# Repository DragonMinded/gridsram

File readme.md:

A set of utilities for interfacing with a M48Z128-85PM1 battery-backed SRAM chip that has been used in The Grid by Midway. This is the chip that stores all of the player profiles so that players can track their statistics, name and call name across different games. It also stores all the single player tower clear records for the cabinet. The ``ArduinoSRAMReader`` directory contains an Arduino sketch that can interface with the ``dump.py`` utility inside the ``GridUtilities`` directory. When used together, an SRAM chip can be partially or fully read or written. The ``print.py`` utility takes a dumped 128KB SRAM file (or a MAME ``nvram`` file) and prints profiles and tower clear records contained in it. The ``editor.py`` utility presents a curses interface where you can add, edit and delete profiles from an SRAM file (or a MAME ``nvram`` file) as well as reset tower clear records for various towers.

All of the scripts require Python 3.6 or greater due to their use of type hints. The ``editor.py`` script additionally requires that [dragoncurses](https://github.com/DragonMinded/dragoncurses) be installed. All utilites are meant to be run from the commandline and all utilities include help. Edited profiles are fully compatible with both the emulated MAME release of The Grid as well as actual arcade hardware. If everything is working correctly, it should take about a minute to dump a full SRAM chip and about a minute and a half to write a full SRAM chip.

## Running the Utilities

Utilities can all be run from the commandline on any operating system with Python 3.6 or greater in the path. All of them support help, so you should start by running any of the utilities with the "--help" flag in order to see more of the utility's operation. All utilities should be run from within the `GridUtilities` folder.

### dump.py

A simple utility that can interface with hardware as built below and plugged into a programmed Arduino. It can perform a read or a write action. Run it like so to see options:

```
python3 dump.py --help
```

Note that depending on your operating system, the default port will not work and you will have to specify it directly. On MacOS and Linux, you can run `ls /dev/tty*` and your Arduino will probably be the only one listed. On Windows, you will have to specify the com port such as "COM1" that the Arduino is connected to.

### print.py

A simple parsing utility that will read an SRAM dumped from "dump.py" or taken from MAME and print out one or more profiles and tower clear records contained inside it. Run it like so to see options:

```
python3 print.py --help
```

### editor.py

A text-based UI for editing profiles on a SRAM dumped from "dump.py" or taken from MAME. Note that this requires [dragoncurses](https://github.com/DragonMinded/dragoncurses) be installed in order to operate properly! It can create new profiles, delete profiles, and edit the details of any existing profile including the PIN, name, call sign and other details. Run it like so to see options:

```
python3 editor.py --help
```

## Arduino Schematic for Real Hardware

The following is a simple schematic that I built in order to edit profiles on an SRAM chip that I had in my posession. I've connected the 8 bidirectional data lines directly to 8 Arduino pins. I've connected two Arduino pins through inverters to the write enable and output enable lines to programatically select read/write mode. I've connected two Arduino pins to three serial to parallel shift registers in order to drive the necessary 17 address lines from two Arduino pins. If you use the same Arduino line, tied directly to the output enable line, and through an inverter to the write enable line (ensuring startup defaults to read), you can probably get away with using only two shift registers and tying A16 directly to the unused Arduino pin. I have not tested this. I have not included decoupling capacitors or a power supply. I recommend 0.1uF decoupling capacitors for each chip including the M48Z128. The datasheet for the SRAM also recommends a 1N5817 diode connected between its VCC and GND pins to protect against data loss when powering the chip. You should be able to take +5V and GND from the Arduino and it will supply enough voltage. I assume that you can either build your own CMOS inverters using BJTs or use a 7400 series inverter chip such as a quad NAND gate with both inputs tied together for each gate. When referring to a free floating pin, this indicates a connection to an Arduino Uno pin. In order to make an ASCII diagram possible, connections between the 74LS164 shift registers handling the address logic and the M48Z128 chip are not drawn. Instead they are labelled. It goes without saying but if you use an external PSU to provide +5V, connect the grounds from the Arduino, all of the ground points in the diagram, and the PSU.

                                                        o +5V pin
                           +-----------------------+    |
                           |1  NC            VCC 32|----/
      74LS164 3 Qa (3)-----|2  A16           A15 31|-----74LS164 2 Qh (13)
     74LS164 2 Qg (12)-----|3  A14            NC 30|                                           /|
     74LS164 2 Qe (10)-----|4  A12            !W 29|-----------------------------------------o |-----o Pin 12
     74LS164 1 Qh (13)-----|5  A7      M     A13 28|-----74LS164 2 Qf (11)                     \|
     74LS164 1 Qg (12)-----|6  A6      4      A8 27|-----74LS164 2 Qa (3)
     74LS164 1 Qf (11)-----|7  A5      8      A9 26|-----74LS164 2 Qb (4)
     74LS164 1 Qe (10)-----|8  A4      Z     A11 25|-----74LS164 2 Qd (6)                      /|
      74LS164 1 Qd (6)-----|9  A3      1      !G 24|-----------------------------------o |-----o Analog Pin 2
      74LS164 1 Qc (5)-----|10 A2      2     A10 23|-----74LS164 2 Qc (5)                      \|
      74LS164 1 Qb (4)-----|11 A1      8      !E 22|----------------o GND (chip always enbled)
      74LS164 1 Qa (3)-----|12 A0            DQ7 21|-----o Pin 9
               Pin 2 o-----|13 DQ0           DQ6 20|-----o Pin 8
               Pin 3 o-----|14 DQ1           DQ5 19|-----o Pin 7
               Pin 4 o-----|15 DQ2           DQ4 18|-----o Pin 6
                      /----|16 GND           DQ3 17|-----o Pin 5
                      |    +-----------------------+
              GND pin o
   
                                   74LS164 1         o +5V pin
                              +-----------------+    |
                 Pin 10 o-----|1  A       VCC 14|----/
     +5V pin o----------------|2  B        Qh 13|-----A7 (5) and 74LS164 2 A (1)
                  A0 (12)-----|3  Qa       Qg 12|-----A6 (6)
                  A1 (11)-----|4  Qb       Qf 11|-----A5 (7)
                  A2 (10)-----|5  Qc       Qe 10|-----A4 (8)
                   A3 (9)-----|6  Qd     !CLR  9|---------------o +5V pin
                         /----|7  GND     CLK  8|-----o Pin 11
                         |    +-----------------+
                 GND pin o
   
                                   74LS164 2         o +5V pin
                              +-----------------+    |
        74LS164 1 Qh (13)-----|1  A       VCC 14|----/
     +5V pin o----------------|2  B        Qh 13|-----A15 (31) and 74LS164 3 A (1)
                  A8 (27)-----|3  Qa       Qg 12|-----A14 (3)
                  A9 (26)-----|4  Qb       Qf 11|-----A13 (28)
                 A10 (23)-----|5  Qc       Qe 10|-----A12 (4)
                 A11 (25)-----|6  Qd     !CLR  9|---------------o +5V pin
                         /----|7  GND     CLK  8|-----o Pin 11
                         |    +-----------------+
                 GND pin o
   
                                   74LS164 3         o +5V pin
                              +-----------------+    |
      74LS164 2 Qh (13) o-----|1  A       VCC 14|----/
     +5v pin o----------------|2  B        Qh 13|
                  A16 (2)-----|3  Qa       Qg 12|
                              |4  Qb       Qf 11|
                              |5  Qc       Qe 10|
                              |6  Qd     !CLR  9|---------------o Connect to +5v to disable
                         /----|7  GND     CLK  8|-----o Pin 11
                         |    +-----------------+
                 GND pin o

## PCB and KiCad Schematic

If you don't want to hand-wire a circuit, I have tested out an Arduino shield board that you can have manufactured and then assemble yourself. If you just want to get a board manufactured, check out https://oshpark.com/shared_projects/tCR4N9Gb which has the BOM as well as the board laid out and ready to be ordered. You will still need to assemble the board yourself which requires some soldering experience. For the source files (made in KiCad), check out the `Board/` folder.

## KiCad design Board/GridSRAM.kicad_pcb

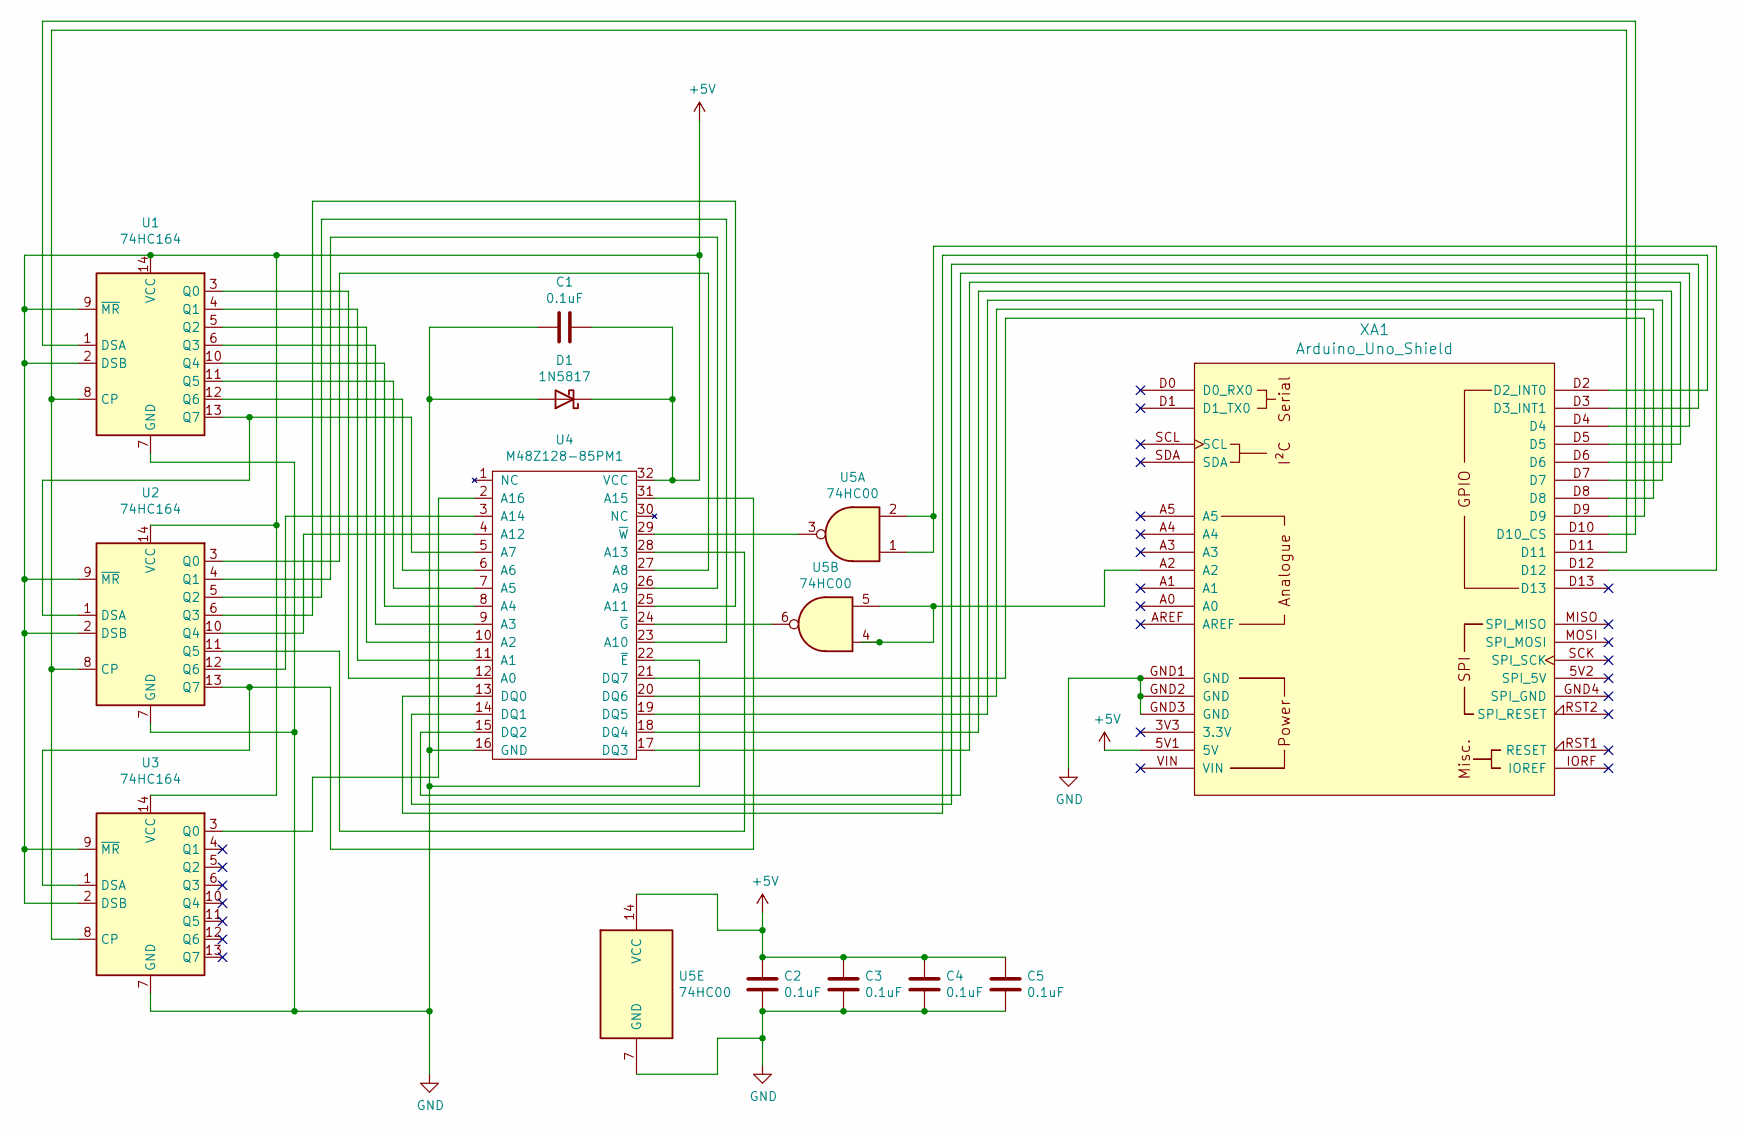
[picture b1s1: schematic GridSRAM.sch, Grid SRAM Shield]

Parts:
C1, C2, C3, C4, C5: 0.1uF; C_Disc_D4.3mm_W1.9mm_P5.00mm
D1: 1N5817; D_DO-41_SOD81_P10.16mm_Horizontal
U1, U2, U3: 74HC164; DIP-14_W7.62mm_Socket
U4: M48Z128-85PM1
U5: 74HC00; DIP-14_W7.62mm_Socket
XA1: Arduino_Uno_Shield

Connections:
+5V: C1.1, C2.1, C3.1, C4.1, C5.1, D1.1 (K), U1.2 (DSB), U1.9 (~MR), U1.14 (VCC), U2.2 (DSB), U2.9 (~MR), U2.14 (VCC), U3.2 (DSB), U3.9 (~MR), U3.14 (VCC), U4.32 (VCC), U5.14 (VCC), XA1.5V1 (5V)
GND: C1.2, C2.2, C3.2, C4.2, C5.2, D1.2 (A), U1.7 (GND), U2.7 (GND), U3.7 (GND), U4.16 (GND), U4.22 (~E), U5.7 (GND), XA1.GND1 (GND), XA1.GND2 (GND), XA1.GND3 (GND)
unnamed: U1.1 (DSA), XA1.D10 (D10_CS)
unnamed: U1.3 (Q0), U4.12 (A0)
unnamed: U1.4 (Q1), U4.11 (A1)
unnamed: U1.5 (Q2), U4.10 (A2)
unnamed: U1.6 (Q3), U4.9 (A3)
unnamed: U1.8 (CP), U2.8 (CP), U3.8 (CP), XA1.D11
unnamed: U1.10 (Q4), U4.8 (A4)
unnamed: U1.11 (Q5), U4.7 (A5)
unnamed: U1.12 (Q6), U4.6 (A6)
unnamed: U1.13 (Q7), U2.1 (DSA), U4.5 (A7)
unnamed: U2.3 (Q0), U4.27 (A8)
unnamed: U2.4 (Q1), U4.26 (A9)
unnamed: U2.5 (Q2), U4.23 (A10)
unnamed: U2.6 (Q3), U4.25 (A11)
unnamed: U2.10 (Q4), U4.4 (A12)
unnamed: U2.11 (Q5), U4.28 (A13)
unnamed: U2.12 (Q6), U4.3 (A14)
unnamed: U2.13 (Q7), U3.1 (DSA), U4.31 (A15)
unnamed: U3.3 (Q0), U4.2 (A16)
unnamed: U4.13 (DQ0), XA1.D2 (D2_INT0)
unnamed: U4.14 (DQ1), XA1.D3 (D3_INT1)
unnamed: U4.15 (DQ2), XA1.D4
unnamed: U4.17 (DQ3), XA1.D5
unnamed: U4.18 (DQ4), XA1.D6
unnamed: U4.19 (DQ5), XA1.D7
unnamed: U4.20 (DQ6), XA1.D8
unnamed: U4.21 (DQ7), XA1.D9
unnamed: U4.24 (~G), U5.6
unnamed: U4.29 (~W), U5.3
unnamed: U5.1, U5.2, XA1.D12
unnamed: U5.4, U5.5, XA1.A2

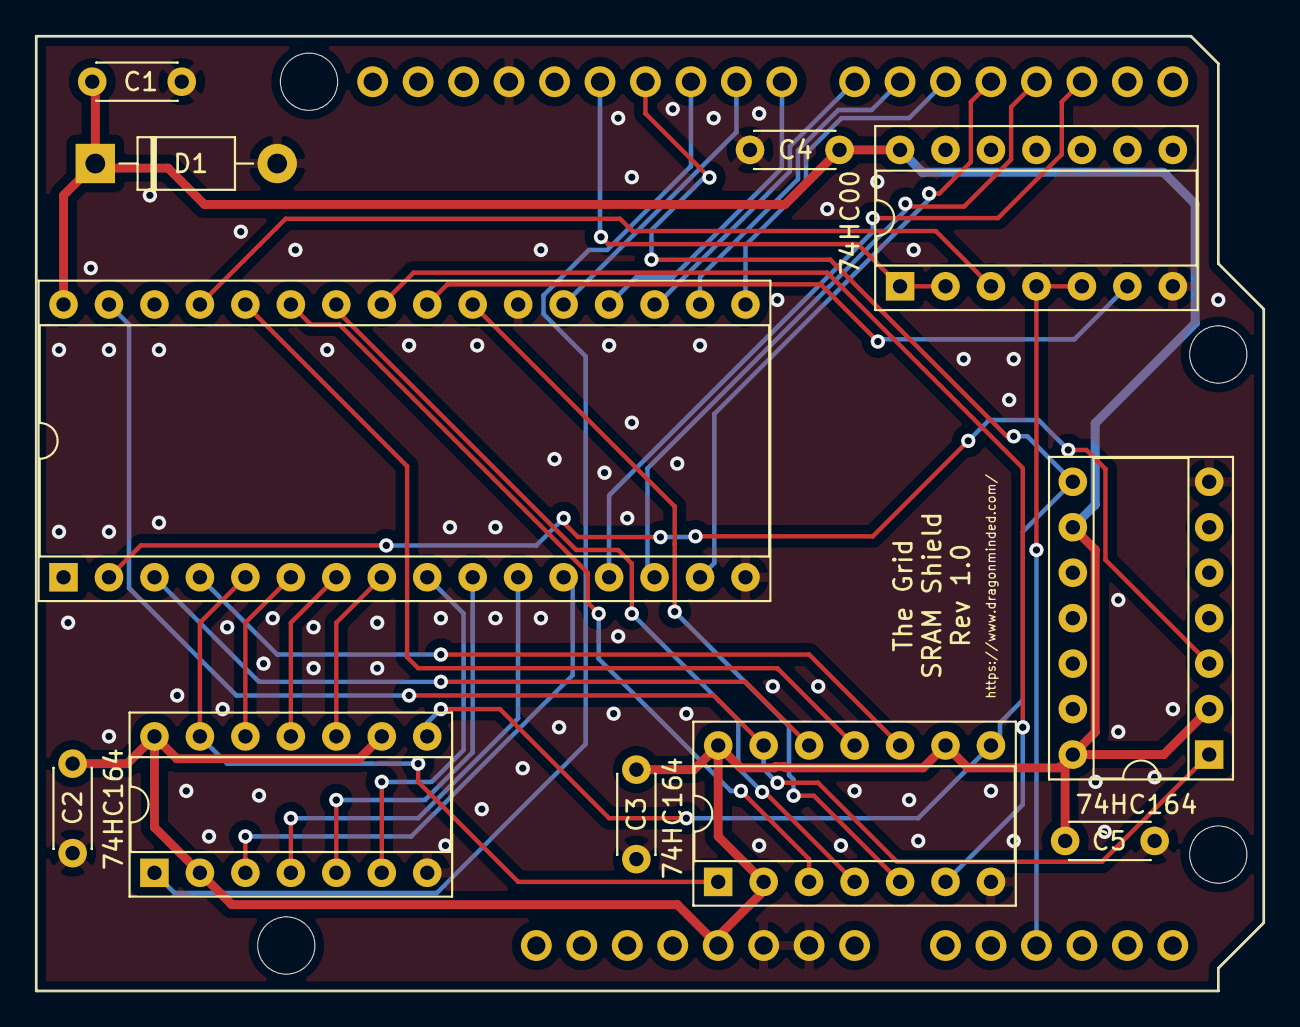
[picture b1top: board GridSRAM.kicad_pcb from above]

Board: 2 copper layers, 68.6 x 53.3 mm, 12 parts (0 on the bottom side), 33 nets.

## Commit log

2019-01-04 Initial commit of protocol.
2019-01-05 Add a .gitignore.
2019-01-05 Hook up to digital IO and shift registers to actually read SRAM chip.
2019-01-05 Bugfix for reading small values, add byte/wordswap utilities.
2019-01-05 Add a dump utility to start exercising code.
2019-01-11 Hook up OE/WE and implement chip write.
2019-01-11 Fix bug where we don't recognize an error response during a continue.
2019-01-13 Split byte utilities out to their own file.
2019-01-13 Initial check-in of profile RE.
2019-01-13 Apply some flake8 and mypy fixes.
2019-01-26 Ignore mypy files.
2019-01-26 Allow hex specification of offset/length as well as decimal.
2019-01-26 Fix horrid global reference, support scanning entire chip for profiles.
2019-02-02 Additional reverse engineering of the profile format.
2019-02-02 Additional profile reverse engineering complete.
2019-02-03 Clean up profile code, add frontend utility, add profile collection helper.
2019-02-03 Add another reversed field, make printout prettier.
2019-02-03 Finish RE on important fields.
2019-02-03 Add documentation for the rest of the fields.
2019-02-03 Make profile create set the data flag correctly.
2019-02-03 Proper profile limit, plus preserve the rest of the chip.
2019-02-05 Finish RE on 3 of the 4 remaining bytes, document the last one. Fix up clearing a profile to not create a new object reference and also properly initialize the checksum.
2019-02-05 Rename grid utilities directory to be more accurate.
2019-02-05 Better help for print utility.
2019-02-05 Add initial version of profile editor. Currently can display profiles on a list and delete them.
2019-02-06 Allow clicking on the profile list to select.
2019-02-06 Slight improvements to grid list component.
2019-02-06 Minor fixes to profile object.
2019-02-06 Hook up editor dialog with validation and such.
2019-02-06 Hook up the ability to add a new profile.
2019-02-07 Add ability to change control mode. Fix clicking on main profile to properly constrain to the list.
2019-02-07 Real fix for idle CPU usage applied to dragoncurses upstream.
2019-02-09 Apply caching to speed up rendering list.
2019-02-09 Handle scroll window for profile list.
2019-02-09 Fix delete not busting cache, add home/end/pgup/pgdn support to list.
2019-02-09 Address todos by inserting LUT for call sign to call name.
2019-02-09 Add right click context menu to grid list.
2019-02-09 Support double-click to edit.
2019-02-09 Add support for scrolling with mouse.
2019-02-09 Make script frontends executable.
2019-02-09 Add a readme for the project.
2019-02-09 Put the readme in the right place -_-;
2019-02-09 Better fit for schematic.
2019-02-09 Format schematic a bit more.
2019-02-09 Consistency in VCC/GND for all chips.
2020-08-09 Fix inability to create a new profile on an empty SRAM file.
2021-01-02 Move OE pin to Analog Pin 2 to avoid flickering LED problem with pin 13.
2021-01-02 Add additional details for schematic.
2021-01-03 Get rid of unnecessary delays, speed up reading/writing by a bunch.
2021-01-03 Fix writes that need slower data transmission, update readme with expected read and write times.
2021-01-20 Update readme with link to PCB.
2021-01-20 Add KiCad project so sources for PCB are available.
2021-06-27 Remove unrelated binary utilities so I can move them to arcadeutils.
2022-04-15 Update readme with more details on running utilities.
2022-04-15 Update editor to allow for tower level 10 to be selected, also allow creating an SRAM file from scratch when editing.
2022-04-23 Add requirements.txt file for running the utilities, ignore SRAM dumps.
2022-08-06 Fix problem reading/writing 10 digit PINs when the first digit is non-zero.
2022-09-24 Shuffle around some backend stuff to be able to round-trip things other than profiles.
2022-09-24 Add a few utilities to easily convert between cabinet and MAME nvram formats for testing.
2022-09-24 Add ability to read and update tower clear times to backend, creating a new SRAM from scratch in the editor is accepted by the game now.
2022-09-25 When creating a blank SRAM or clearing out tower clears, put the correct times in based on a freshly cleared SRAM from the game.
2022-09-25 Fix type hints now that dragoncurses is fully typed.
2022-09-25 Format with black, fix flake errors, introduce flake config.
2022-09-25 Fix type issues discovered when enabling strict mode.
2022-09-25 Add ability to view and reset tower clear records for a given SRAM dump.
2022-09-25 Add a horizontal divider to the label at the bottom to make the tabbed component look better.
2022-09-25 Make a few of the labels clickable so the whole UI can be used with a mouse.
2023-09-04 Add explicit public domain license file.
